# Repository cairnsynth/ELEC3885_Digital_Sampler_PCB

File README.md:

# ELEC3885 Digital Sampler PCB

- Sample-based musical instrument aimed for use in education
- Capable of sequencing and playback of samples on 4 separate channels, and audio effects
- Developed using the Teensy 4.1 development board

## PCB Features

- USB/Li-Po battery power supply
- Audio I/O
	- Line level input/output
	- Headphone output with variable volume
	- Internal MEMS microphone
	- Balanced external microphone input
- User Interface
	- LCD
		- Sample information
		- File browser
		- Parameter values linked to encoders
	- Encoders
		- Control sample specific parameters
	- Potentiometers
		- Control global effects (reverb, filter)
	- RGB LEDs
		- Display sequence playback
	- Button Arrays
		- 8 button array for sample sequencing
		- 4 button array for instant sample playback

---

## Revisions

- Revisions are separated on different branches

### Rev1 (main branch)
- Initial prototype PCB layout containing
	- Teensy 4.1 mounting headers
	- SGTL5000 codec
	- Audio I/O
	- Breakout headers for internal microphone and differential amplifier testing
	- Basic UI

### Rev2
- Layout alterations reducing length of traces for MCU-codec interfaces

### Rev3
- Switch to 4 layer board, 2 sided assembly
	- Analogue circuitry moved to back face
- External microphone differential amplifier added
- Power supply/Li-Po charging circuit added
- Integration of other group members work
	- LCD header and interface routing
	- LED and shift registers
	- Button arrays
	- Encoders/Pots
- Test points added for testing/debugging

### Rev4
- Changes to accommodate JLCPCB stock
	- Codec circuit redesign for QFN32 package of SGTL5000
	- SMD packages
- Trace teardrops added

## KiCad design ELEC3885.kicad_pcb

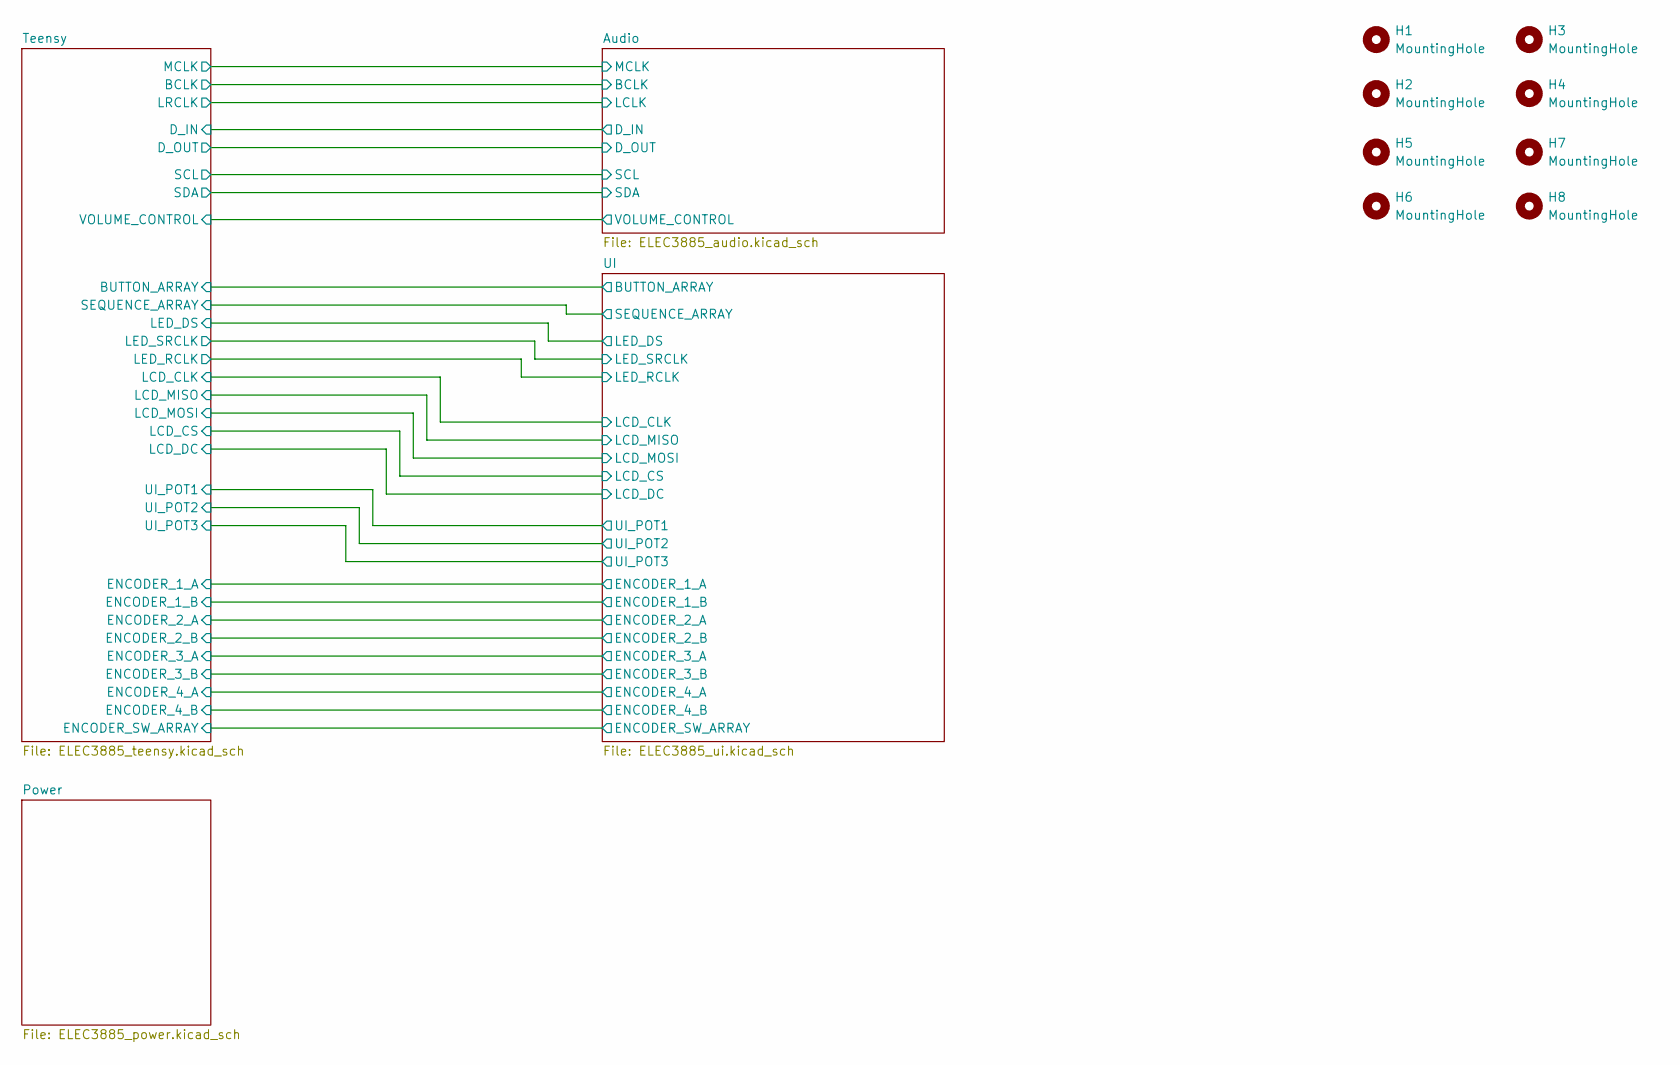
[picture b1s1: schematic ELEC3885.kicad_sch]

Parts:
H1, H2, H3, H4, H5, H6, H7, H8: MountingHole; MountingHole_3.2mm_M3

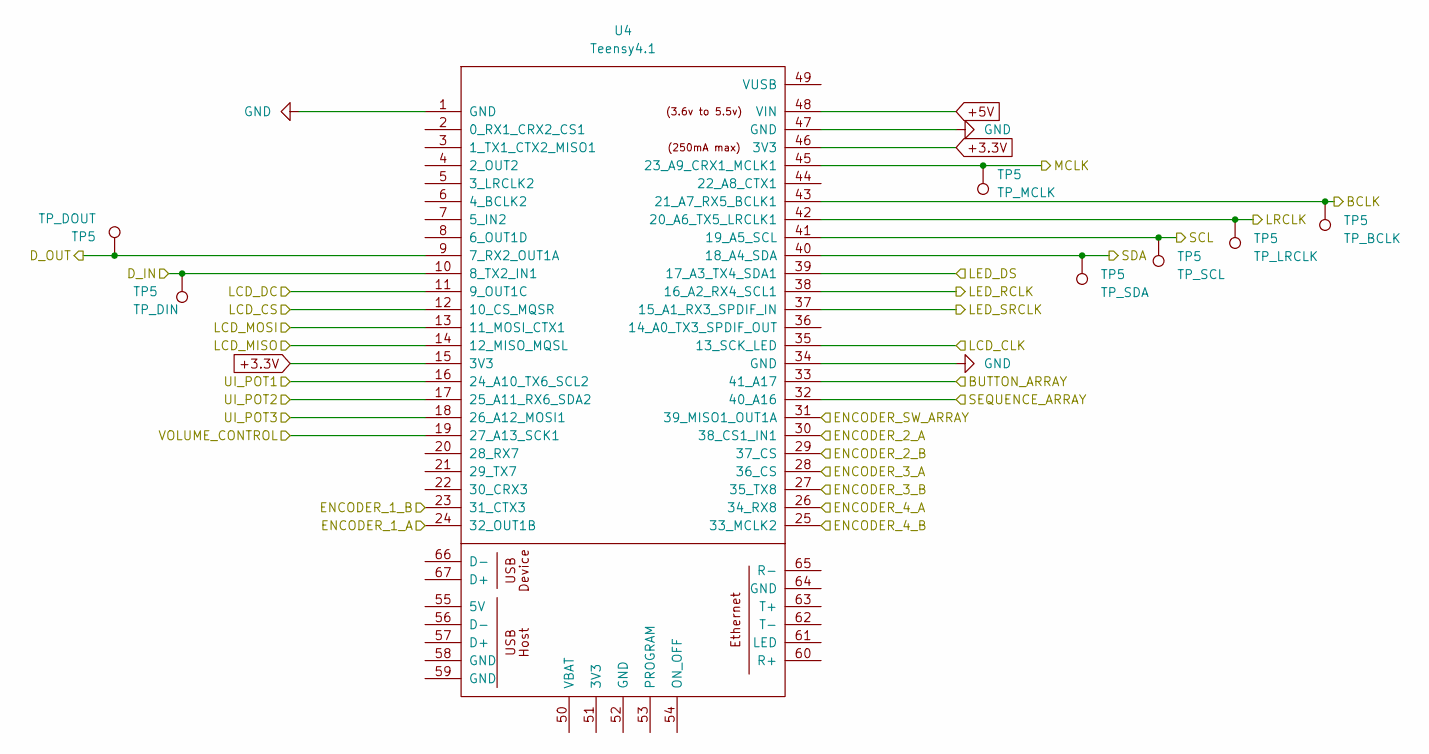
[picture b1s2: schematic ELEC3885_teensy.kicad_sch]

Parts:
TP5: TP_LRCLK; TestPoint_Pad_D1.0mm
U4: Teensy4.1; Teensy41

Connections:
+3.3V: U4.15 (3V3), U4.46 (3V3); also elsewhere on the board
+5V: U4.48 (VIN); also elsewhere on the board
/Audio/VOLUME_CONTROL: U4.19 (27_A13_SCK1); also elsewhere on the board
/Teensy/ENCODER_1_A: U4.24 (32_OUT1B); also elsewhere on the board
/Teensy/ENCODER_1_B: U4.23 (31_CTX3); also elsewhere on the board
/Teensy/ENCODER_2_A: U4.30 (38_CS1_IN1); also elsewhere on the board
/Teensy/ENCODER_2_B: U4.29 (37_CS); also elsewhere on the board
/Teensy/ENCODER_3_A: U4.28 (36_CS); also elsewhere on the board
/Teensy/ENCODER_3_B: U4.27 (35_TX8); also elsewhere on the board
/Teensy/ENCODER_4_A: U4.26 (34_RX8); also elsewhere on the board
/Teensy/ENCODER_4_B: U4.25 (33_MCLK2); also elsewhere on the board
/Teensy/ENCODER_SW_ARRAY: U4.31 (39_MISO1_OUT1A); also elsewhere on the board
/Teensy/LCD_CLK: U4.35 (13_SCK_LED); also elsewhere on the board
/Teensy/LCD_CS: U4.12 (10_CS_MQSR); also elsewhere on the board
/Teensy/LCD_DC: U4.11 (9_OUT1C); also elsewhere on the board
/Teensy/LCD_MISO: U4.14 (12_MISO_MQSL); also elsewhere on the board
/Teensy/LCD_MOSI: U4.13 (11_MOSI_CTX1); also elsewhere on the board
/Teensy/LED_DS: U4.39 (17_A3_TX4_SDA1); also elsewhere on the board
/Teensy/LED_RCLK: U4.38 (16_A2_RX4_SCL1); also elsewhere on the board
/Teensy/LED_SRCLK: U4.37 (15_A1_RX3_SPDIF_IN); also elsewhere on the board
/Teensy/SEQUENCE_ARRAY: U4.32 (40_A16); also elsewhere on the board
/Teensy/UI_POT1: U4.16 (24_A10_TX6_SCL2); also elsewhere on the board
/Teensy/UI_POT2: U4.17 (25_A11_RX6_SDA2); also elsewhere on the board
/Teensy/UI_POT3: U4.18 (26_A12_MOSI1); also elsewhere on the board
GND: U4.1 (GND), U4.34 (GND), U4.47 (GND); also elsewhere on the board

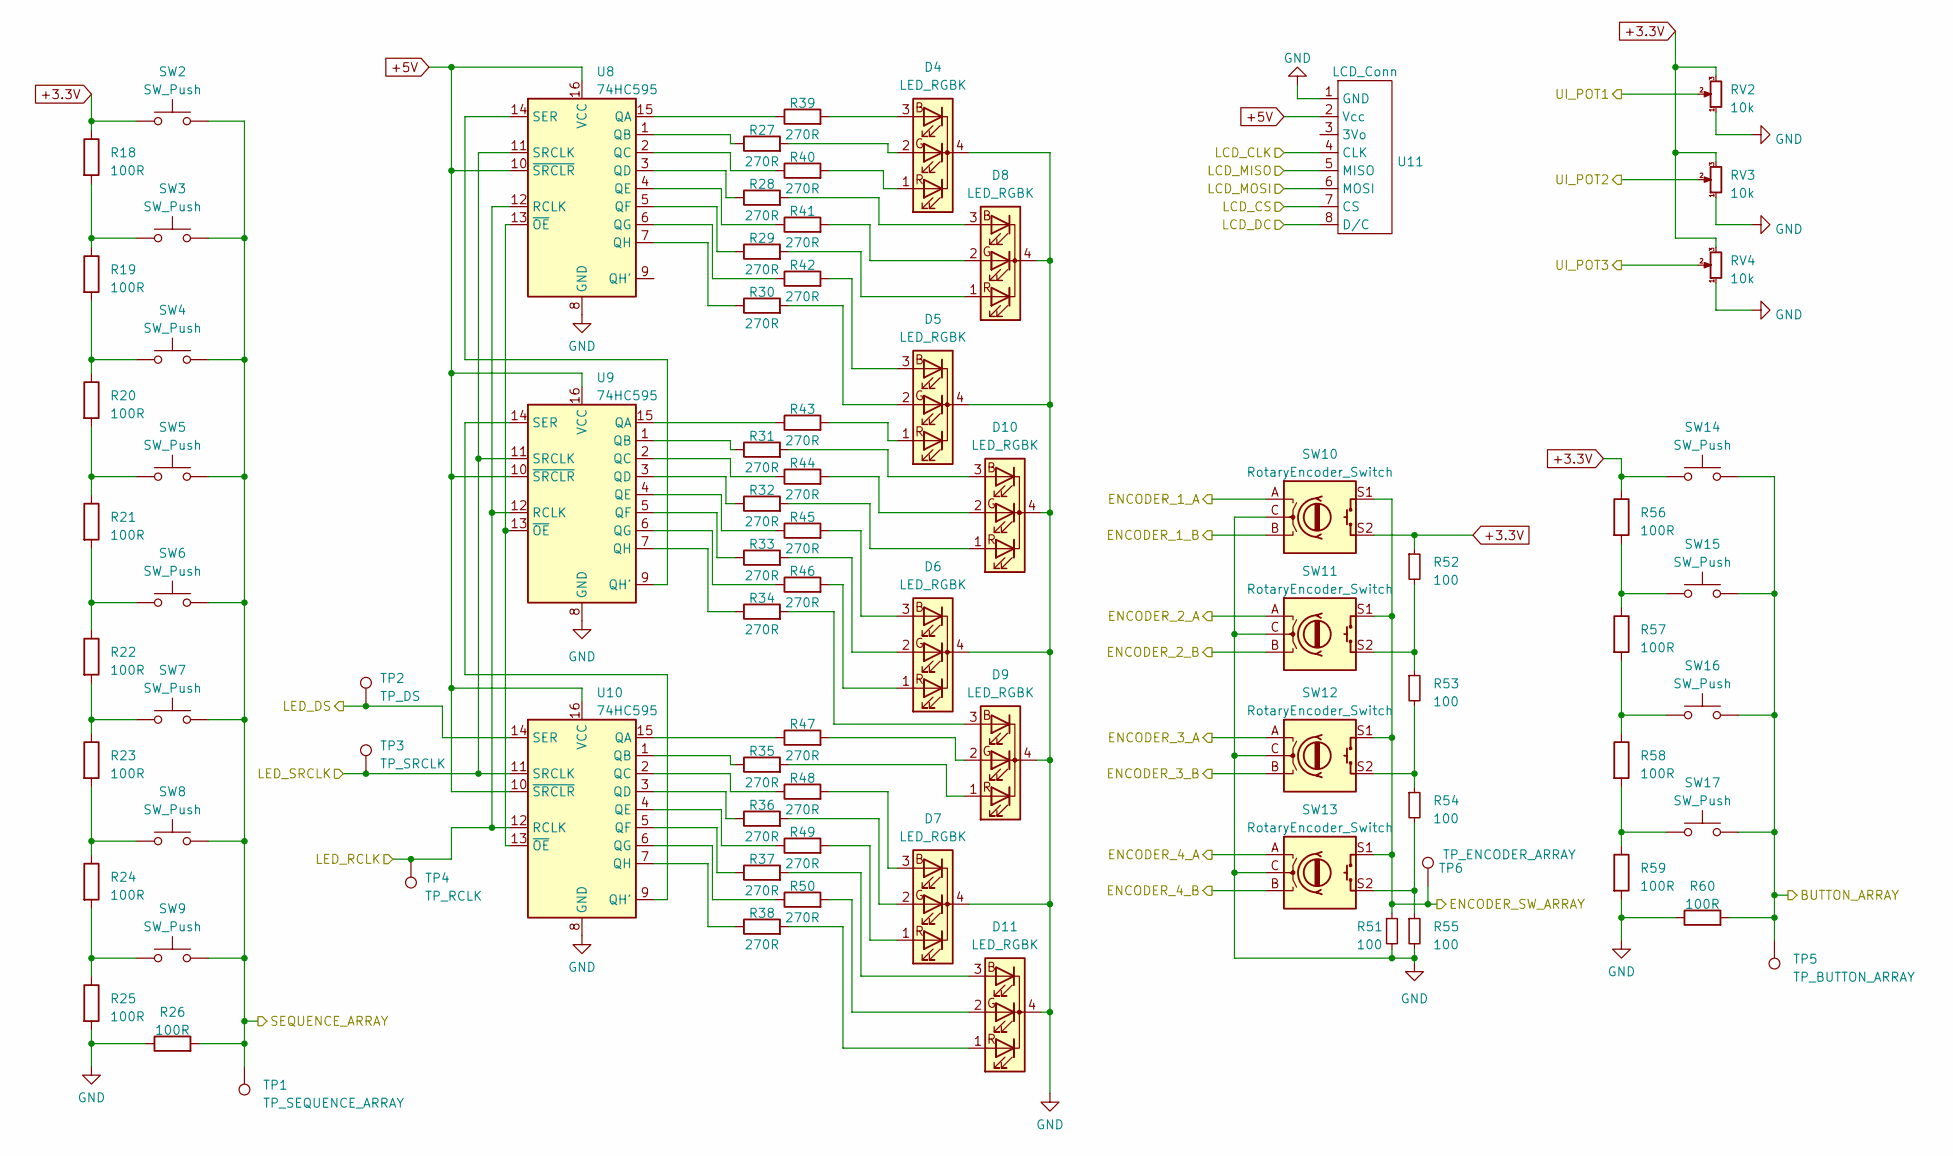
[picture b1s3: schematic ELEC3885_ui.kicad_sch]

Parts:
D4, D5, D6, D7, D8, D9, D10, D11: LED_RGBK; LED_D5.0mm-4_RGB
R18, R19, R20, R21, R22, R23, R24, R25, R26, R56, R57, R58, R59, R60: 100R; R_0402_1005Metric
R27, R28, R29, R30, R31, R32, R33, R34, R35, R36, R37, R38, R39, R40, R41, R42, R43, R44, R45, R46, R47, R48, R49, R50: 270R; R_0402_1005Metric
R51, R52, R53, R54, R55: 100; R_0402_1005Metric
RV2, RV3, RV4: 10k; Potentiometer_Alpha_RD901F-40-00D_Single_Vertical
SW2, SW3, SW4, SW5, SW6, SW7, SW8, SW9, SW14, SW15, SW16, SW17: SW_Push; SW_Cherry_MX_1.00u_PCB
SW10, SW11, SW12, SW13: RotaryEncoder_Switch; RotaryEncoder_Alps_EC11E-Switch_Vertical_H20mm
TP1: TP_SEQUENCE_ARRAY; TestPoint_Pad_D1.0mm
TP2: TP_DS; TestPoint_Pad_D1.0mm
TP3: TP_SRCLK; TestPoint_Pad_D1.0mm
TP4: TP_RCLK; TestPoint_Pad_D1.0mm
TP5: TP_BUTTON_ARRAY; TestPoint_Pad_D1.0mm
TP6: TP_ENCODER_ARRAY; TestPoint_Pad_D1.0mm
U8, U9, U10: 74HC595; SOP-16_3.9x9.9mm_P1.27mm
U11: LCD_Conn; Adafruit_3.5_TFT_SPI

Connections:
+3.3V: R18.1, R52.1, R56.1, RV2.3, RV3.3, RV4.3, SW2.1, SW10.S2, SW14.1; also elsewhere on the board
+5V: U8.10 (~SRCLR), U8.16 (VCC), U9.10 (~SRCLR), U9.16 (VCC), U10.10 (~SRCLR), U10.16 (VCC), U11.2 (Vcc); also elsewhere on the board
/Teensy/ENCODER_1_A: SW10.A; also elsewhere on the board
/Teensy/ENCODER_1_B: SW10.B; also elsewhere on the board
/Teensy/ENCODER_2_A: SW11.A; also elsewhere on the board
/Teensy/ENCODER_2_B: SW11.B; also elsewhere on the board
/Teensy/ENCODER_3_A: SW12.A; also elsewhere on the board
/Teensy/ENCODER_3_B: SW12.B; also elsewhere on the board
/Teensy/ENCODER_4_A: SW13.A; also elsewhere on the board
/Teensy/ENCODER_4_B: SW13.B; also elsewhere on the board
/Teensy/ENCODER_SW_ARRAY: R51.1, SW10.S1, SW11.S1, SW12.S1, SW13.S1, TP6.1; also elsewhere on the board
/Teensy/LCD_CLK: U11.4 (CLK); also elsewhere on the board
/Teensy/LCD_CS: U11.7 (CS); also elsewhere on the board
/Teensy/LCD_DC: U11.8 (D/C); also elsewhere on the board
/Teensy/LCD_MISO: U11.5 (MISO); also elsewhere on the board
/Teensy/LCD_MOSI: U11.6 (MOSI); also elsewhere on the board
/Teensy/LED_DS: TP2.1, U10.14 (SER); also elsewhere on the board
/Teensy/LED_RCLK: TP4.1, U8.12 (RCLK), U9.12 (RCLK), U10.12 (RCLK); also elsewhere on the board
/Teensy/LED_SRCLK: TP3.1, U8.11 (SRCLK), U9.11 (SRCLK), U10.11 (SRCLK); also elsewhere on the board
/Teensy/SEQUENCE_ARRAY: R26.2, SW2.2, SW3.2, SW4.2, SW5.2, SW6.2, SW7.2, SW8.2, SW9.2, TP1.1; also elsewhere on the board
/Teensy/UI_POT1: RV2.2; also elsewhere on the board
/Teensy/UI_POT2: RV3.2; also elsewhere on the board
/Teensy/UI_POT3: RV4.2; also elsewhere on the board
GND: D4.4 (K), D5.4 (K), D6.4 (K), D7.4 (K), D8.4 (K), D9.4 (K), D10.4 (K), D11.4 (K), R25.2, R26.1, R51.2, R55.2, R59.2, R60.1, RV2.1, RV3.1, RV4.1, SW10.C, SW11.C, SW12.C, SW13.C, U8.8 (GND), U9.8 (GND), U10.8 (GND), U11.1 (GND); also elsewhere on the board
unnamed: D4.3 (BA), R39.2
unnamed: D4.2 (GA), R27.2
unnamed: D4.1 (RA), R40.2
unnamed: D5.3 (BA), R42.2
unnamed: D5.2 (GA), R30.2
unnamed: D5.1 (RA), R43.2
unnamed: D6.3 (BA), R45.2
unnamed: D6.2 (GA), R33.2
unnamed: D6.1 (RA), R46.2
unnamed: D7.3 (BA), R48.2
unnamed: D7.2 (GA), R36.2
unnamed: D7.1 (RA), R49.2
unnamed: D8.3 (BA), R28.2
unnamed: D8.2 (GA), R41.2
unnamed: D8.1 (RA), R29.2
unnamed: D9.3 (BA), R34.2
unnamed: D9.2 (GA), R47.2
unnamed: D9.1 (RA), R35.2
unnamed: D10.3 (BA), R31.2
unnamed: D10.2 (GA), R44.2
unnamed: D10.1 (RA), R32.2
unnamed: D11.3 (BA), R37.2
unnamed: D11.2 (GA), R50.2
unnamed: D11.1 (RA), R38.2
unnamed: R18.2, R19.1, SW3.1
unnamed: R19.2, R20.1, SW4.1
unnamed: R20.2, R21.1, SW5.1
unnamed: R21.2, R22.1, SW6.1
unnamed: R22.2, R23.1, SW7.1
unnamed: R23.2, R24.1, SW8.1
unnamed: R24.2, R25.1, SW9.1
unnamed: R52.2, R53.1, SW11.S2
unnamed: R53.2, R54.1, SW12.S2
unnamed: R54.2, R55.1, SW13.S2
unnamed: R56.2, R57.1, SW15.1
unnamed: R57.2, R58.1, SW16.1
unnamed: R58.2, R59.1, SW17.1
unnamed: R39.1, U8.15 (QA)
unnamed: R27.1, U8.1 (QB)
unnamed: R40.1, U8.2 (QC)
unnamed: R28.1, U8.3 (QD)
unnamed: R41.1, U8.4 (QE)
unnamed: R29.1, U8.5 (QF)
unnamed: R42.1, U8.6 (QG)
unnamed: R30.1, U8.7 (QH)
unnamed: U8.14 (SER), U9.9 (QH')
unnamed: R43.1, U9.15 (QA)
unnamed: R31.1, U9.1 (QB)
unnamed: R44.1, U9.2 (QC)
unnamed: R32.1, U9.3 (QD)
unnamed: R45.1, U9.4 (QE)
unnamed: R33.1, U9.5 (QF)
unnamed: R46.1, U9.6 (QG)
unnamed: R34.1, U9.7 (QH)
unnamed: R47.1, U10.15 (QA)
unnamed: R35.1, U10.1 (QB)
unnamed: R48.1, U10.2 (QC)
unnamed: R36.1, U10.3 (QD)
unnamed: R49.1, U10.4 (QE)
unnamed: R37.1, U10.5 (QF)
unnamed: R50.1, U10.6 (QG)
unnamed: U9.14 (SER), U10.9 (QH')
unnamed: R38.1, U10.7 (QH)
unnamed: U8.13 (~OE), U9.13 (~OE), U10.13 (~OE)

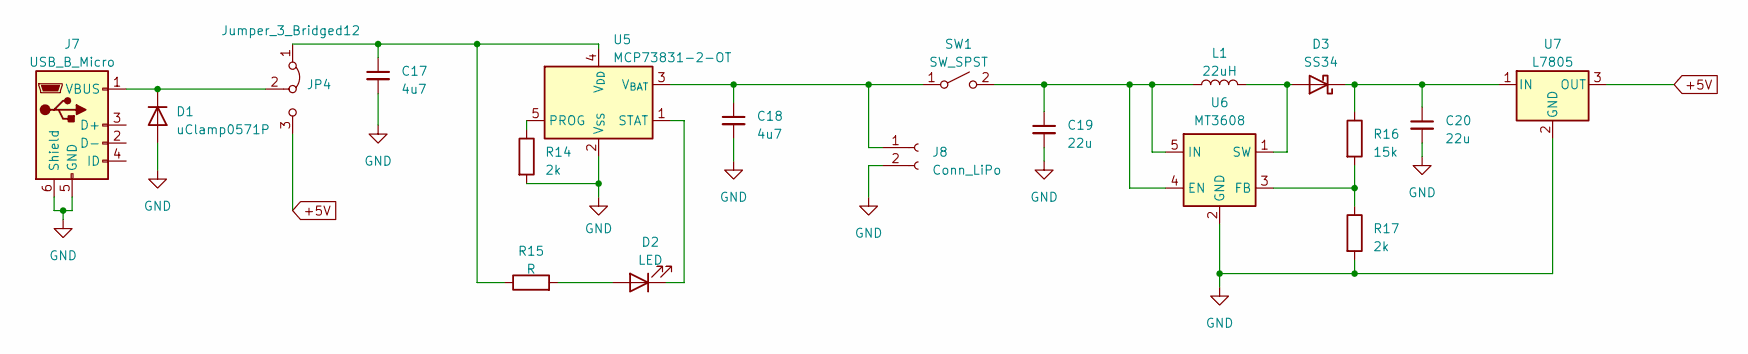
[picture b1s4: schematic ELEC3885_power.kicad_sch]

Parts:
C17, C18: 4u7; C_0603_1608Metric
C19, C20: 22u; C_0603_1608Metric
D1: uClamp0571P; DFN1610-2
D2: LED; LED_0603_1608Metric
D3: SS34; D_SMC
J7: USB_B_Micro; USB_Micro-B_MicroXNJ_Horizontal
J8: Conn_LiPo; JST_EH_S2B-EH_1x02_P2.50mm_Horizontal
JP4: Jumper_3_Bridged12; SolderJumper-3_P1.3mm_Bridged2Bar12_RoundedPad1.0x1.5mm_Num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
L1: 22uH; L_10.4x10.4_H4.8
R14, R17: 2k; R_0402_1005Metric
R15: R; R_0402_1005Metric
R16: 15k; R_0603_1608Metric
SW1: SW_SPST; SW_CuK_OS102011MA1QN1_SPDT_Angled
U5: MCP73831-2-OT; SOT-23-5
U6: MT3608; SOT-23-6
U7: L7805; TO-252-2

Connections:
+5V: JP4.3 (B), U7.3 (OUT); also elsewhere on the board
GND: C17.2, C18.2, C19.2, C20.2, D1.2 (A), J7.5 (GND), J7.6 (Shield), J8.2, R14.2, R17.2, U5.2 (V_{SS}), U6.2 (GND), U7.2 (GND); also elsewhere on the board
unnamed: D1.1 (K), J7.1 (VBUS), JP4.2 (C)
unnamed: D2.2 (A), R15.2
unnamed: D2.1 (K), U5.1 (STAT)
unnamed: D3.2 (A), L1.2, U6.1 (SW)
unnamed: C20.1, D3.1 (K), R16.1, U7.1 (IN)
unnamed: C18.1, J8.1, SW1.1 (A), U5.3 (V_{BAT})
unnamed: C17.1, JP4.1 (A), R15.1, U5.4 (V_{DD})
unnamed: C19.1, L1.1, SW1.2 (B), U6.4 (EN), U6.5 (IN)
unnamed: R14.1, U5.5 (PROG)
unnamed: R16.2, R17.1, U6.3 (FB)

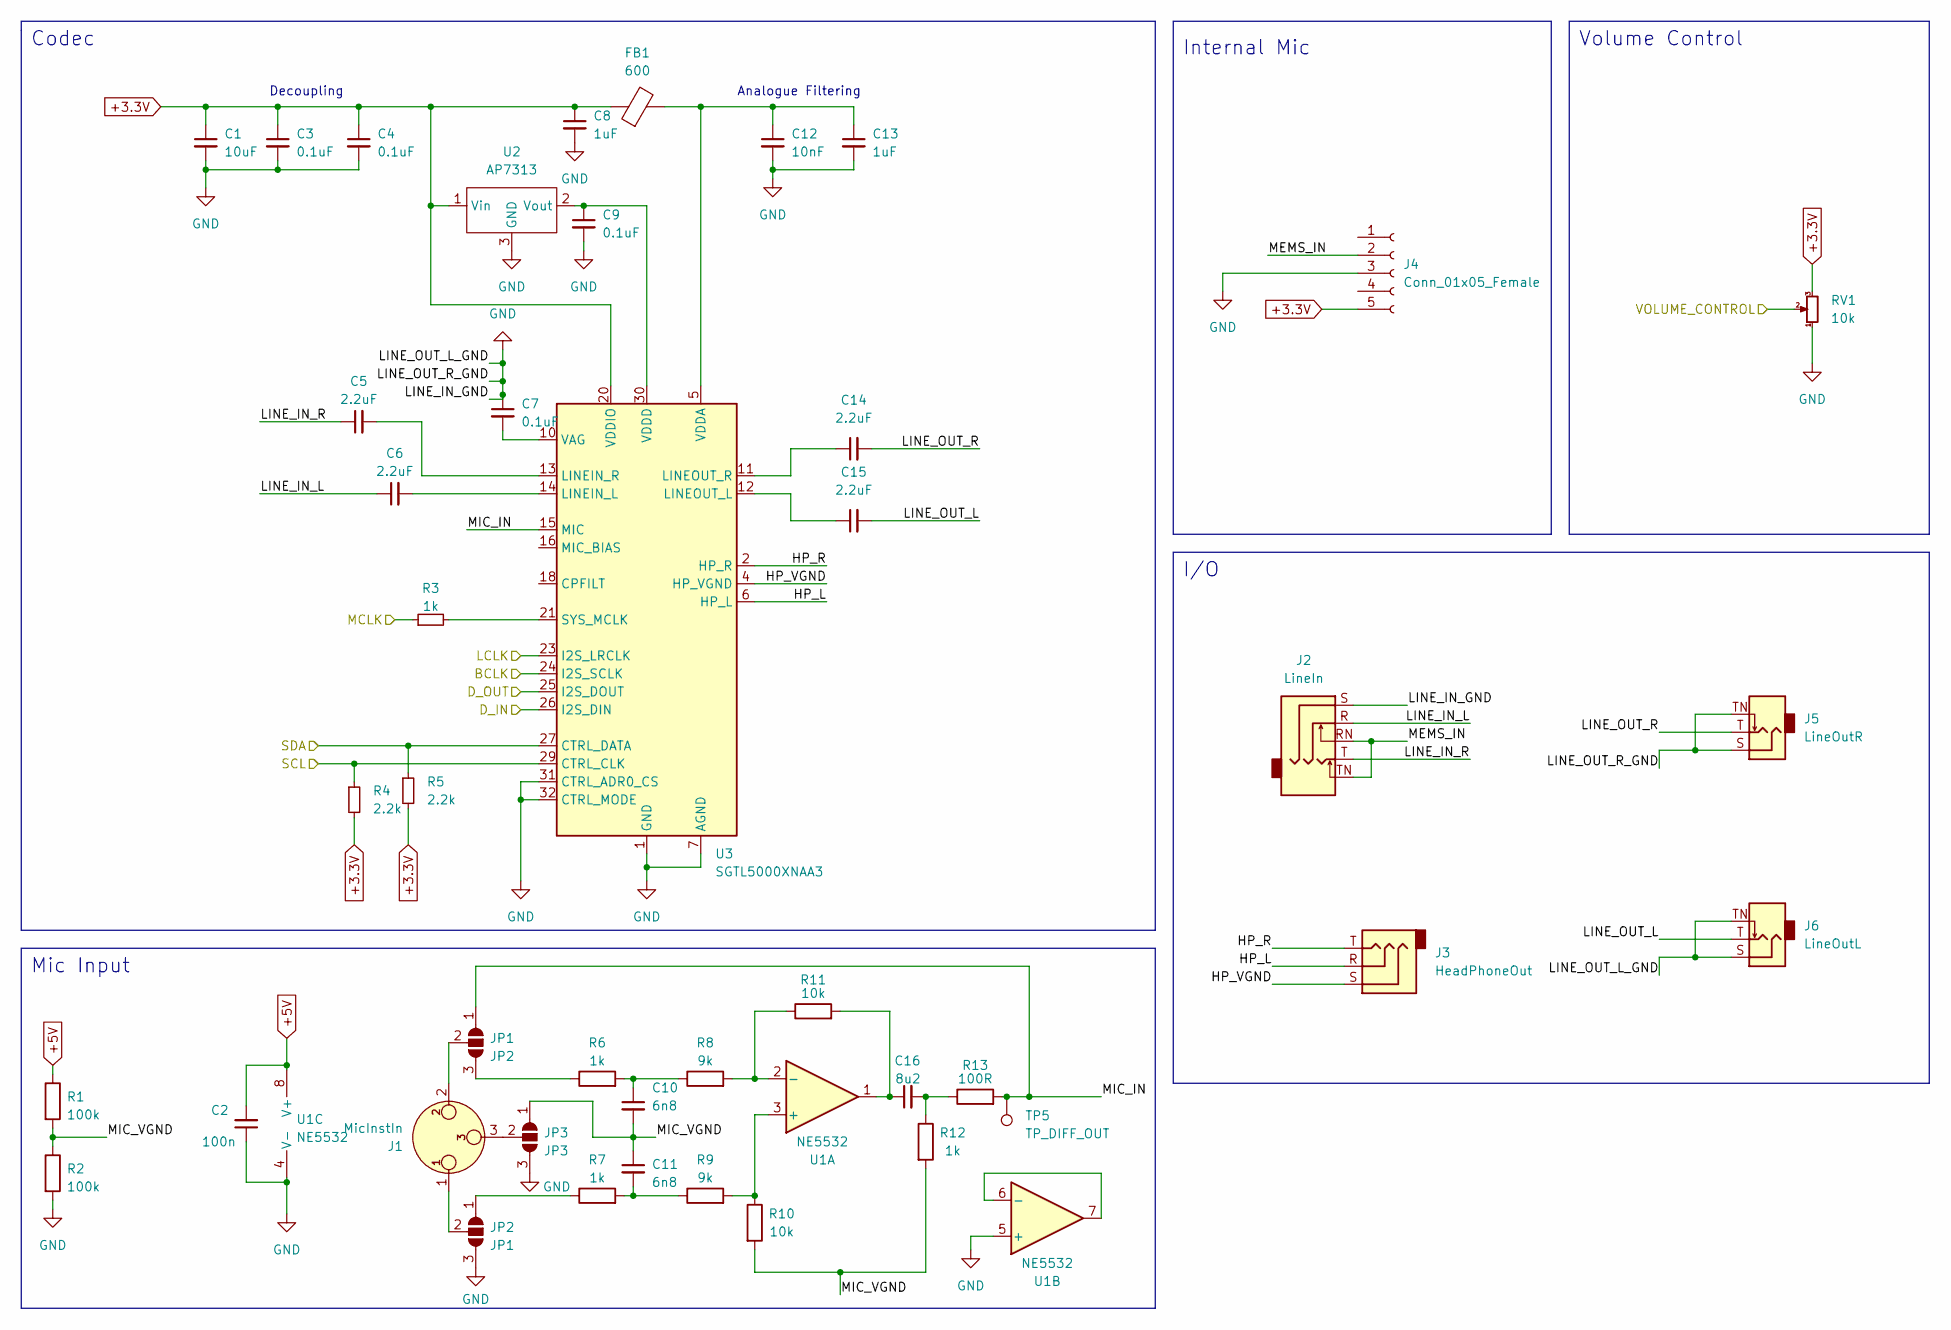
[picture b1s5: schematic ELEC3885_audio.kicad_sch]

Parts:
C1: 10uF; C_0603_1608Metric
C2: 100n; C_0402_1005Metric
C3, C4, C7, C9: 0.1uF; C_0402_1005Metric
C5, C6, C14, C15: 2.2uF; C_0603_1608Metric
C8, C13: 1uF; C_0402_1005Metric
C10, C11: 6n8; C_0402_1005Metric
C12: 10nF; C_0402_1005Metric
C16: 8u2; C_0603_1608Metric
FB1: 600; L_0603_1608Metric
J1: MicInstIn; Jack_XLR_Neutrik_NC3FAAH-0_Horizontal
J2: LineIn; Jack_3.5mm_CUI_SJ1-3535NG_Horizontal
J3: HeadPhoneOut; Jack_3.5mm_CUI_SJ1-3533NG_Horizontal
J4: Conn_01x05_Female; PinSocket_1x05_P2.54mm_Vertical
J5: LineOutR; Jack_6.35mm_Neutrik_NMJ4HCD2_Horizontal
J6: LineOutL; Jack_6.35mm_Neutrik_NMJ4HCD2_Horizontal
JP1: JP2; SolderJumper-3_P1.3mm_Open_RoundedPad1.0x1.5mm
JP2: JP1; SolderJumper-3_P1.3mm_Open_RoundedPad1.0x1.5mm
JP3: JP3; SolderJumper-3_P1.3mm_Open_RoundedPad1.0x1.5mm
R1, R2: 100k; R_0603_1608Metric
R3, R6, R7, R12: 1k; R_0402_1005Metric
R4, R5: 2.2k; R_0402_1005Metric
R8, R9: 9k; R_0805_2012Metric
R10, R11: 10k; R_0603_1608Metric
R13: 100R; R_0402_1005Metric
RV1: 10k; Potentiometer_Alpha_RD901F-40-00D_Single_Vertical
TP5: TP_DIFF_OUT; TestPoint_Pad_D1.0mm
U1: NE5532; SOIC-8-1EP_3.9x4.9mm_P1.27mm_EP2.29x3mm
U2: AP7313; SOT23
U3: SGTL5000XNAA3; QFN-32-1EP_5x5mm_P0.5mm_EP3.6x3.6mm

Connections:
+3.3V: C1.1, C3.1, C4.1, C8.1, FB1.1, J4.5, R4.2, R5.2, RV1.3, U2.1 (Vin), U3.20 (VDDIO); also elsewhere on the board
+5V: C2.2, R1.1, U1.8 (V+); also elsewhere on the board
/Audio/HP_L: J3.R, U3.6 (HP_L)
/Audio/HP_R: J3.T, U3.2 (HP_R)
/Audio/HP_VGND: J3.S, U3.4 (HP_VGND)
/Audio/LINE_IN_L: C6.1, J2.R
/Audio/LINE_IN_R: C5.1, J2.T
/Audio/LINE_OUT_L: C15.2, J6.T
/Audio/LINE_OUT_R: C14.2, J5.T
/Audio/MEMS_IN: J2.RN, J2.TN, J4.2
/Audio/MIC_VGND: C10.2, C11.1, JP3.1 (A), R1.2, R2.1, R10.2, R12.2
/Audio/VOLUME_CONTROL: RV1.2; also elsewhere on the board
GND: C1.2, C2.1, C3.2, C4.2, C7.1, C8.2, C9.2, C12.2, C13.2, J2.S, J4.3, J5.S, J5.TN, J6.S, J6.TN, JP2.3 (B), JP3.3 (B), R2.2, RV1.1, U1.4 (V-), U1.5 (+), U2.3 (GND), U3.1 (GND), U3.3 (GND), U3.7 (AGND), U3.31 (CTRL_ADR0_CS), U3.32 (CTRL_MODE), U3.33 (GND); also elsewhere on the board
unnamed: C10.1, R6.2, R8.1
unnamed: C11.2, R7.2, R9.1
unnamed: C16.1, R11.2, U1.1
unnamed: C16.2, R12.1, R13.1
unnamed: JP1.3 (B), R6.1
unnamed: J1.2, JP1.2 (C)
unnamed: JP2.1 (A), R7.1
unnamed: J1.1, JP2.2 (C)
unnamed: J1.3, JP3.2 (C)
unnamed: R9.2, R10.1, U1.3 (+)
unnamed: R8.2, R11.1, U1.2 (-)
unnamed: U1.6 (-), U1.7
unnamed: C9.1, U2.2 (Vout), U3.30 (VDDD)
unnamed: C6.2, U3.14 (LINEIN_L)
unnamed: C5.2, U3.13 (LINEIN_R)
unnamed: C15.1, U3.12 (LINEOUT_L)
unnamed: C14.1, U3.11 (LINEOUT_R)
unnamed: R3.2, U3.21 (SYS_MCLK)
unnamed: C7.2, U3.10 (VAG)
unnamed: C12.1, C13.1, FB1.2, U3.5 (VDDA)

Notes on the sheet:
Decoupling
Internal Mic
I/O
Volume Control
Codec
Mic Input
Analogue Filtering

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
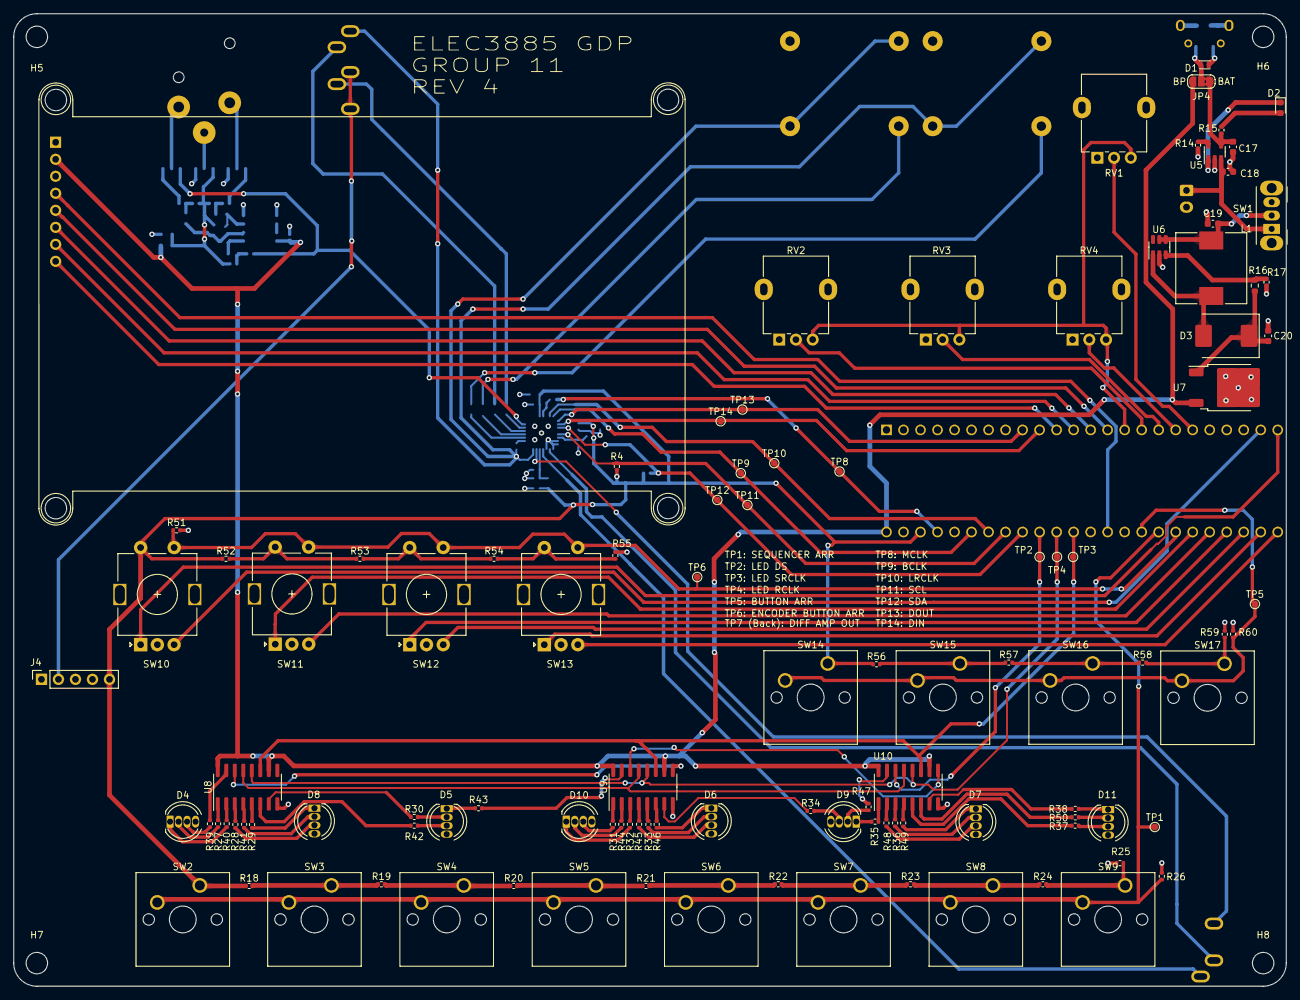
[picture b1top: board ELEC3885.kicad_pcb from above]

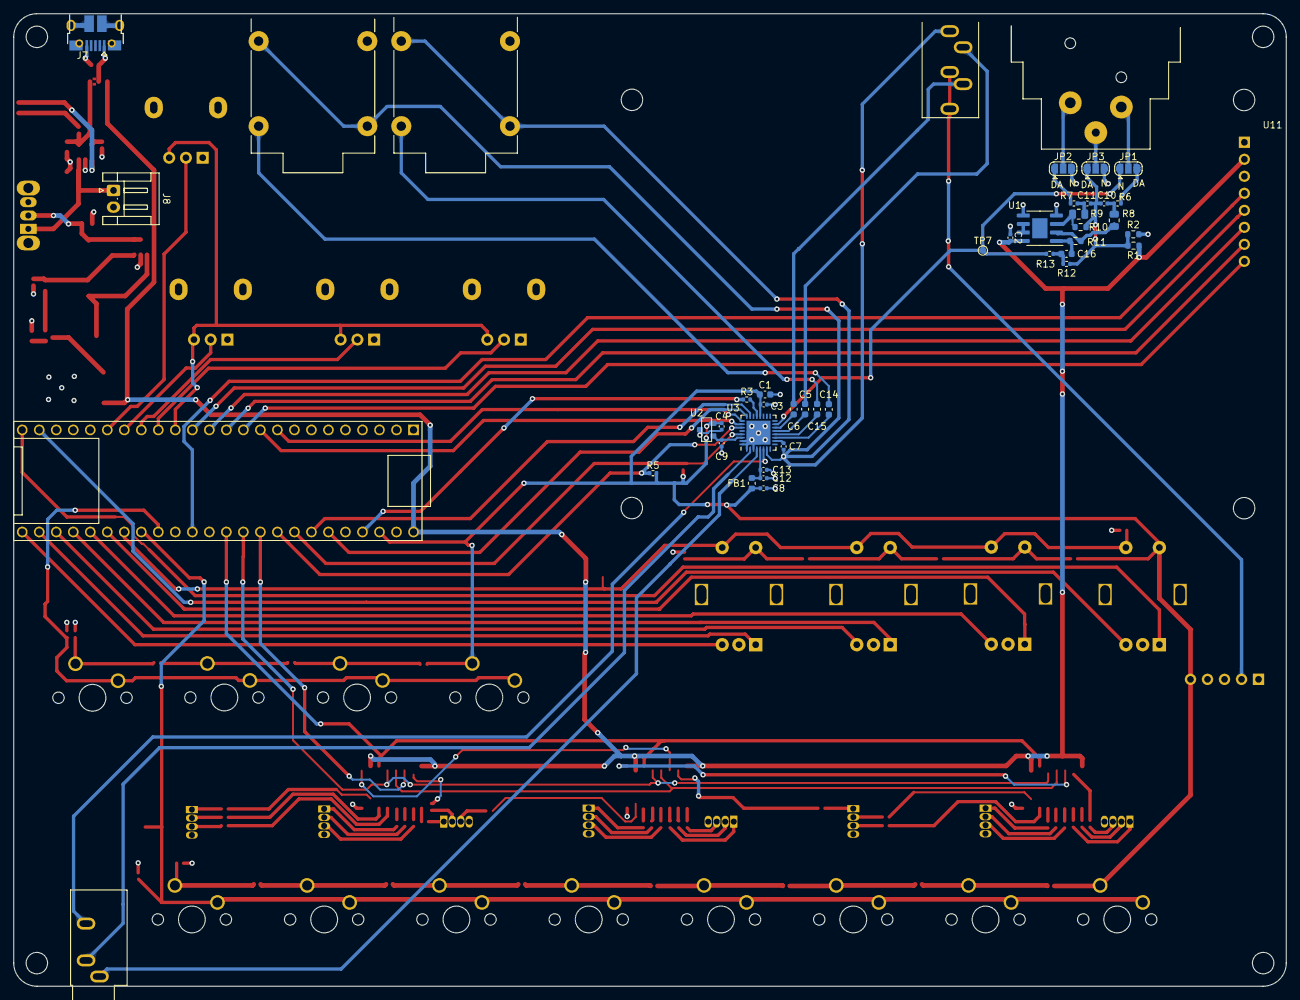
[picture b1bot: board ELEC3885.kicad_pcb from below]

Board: 4 copper layers, 190.0 x 145.2 mm, 159 parts (44 on the bottom side), 137 nets.

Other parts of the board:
TP7: TP_DIFF_OUT; TestPoint_Pad_D1.0mm
TP8: TP_MCLK; TestPoint_Pad_D1.0mm
TP9: TP_BCLK; TestPoint_Pad_D1.0mm
TP10: TP_LRCLK; TestPoint_Pad_D1.0mm
TP11: TP_SCL; TestPoint_Pad_D1.0mm
TP12: TP_SDA; TestPoint_Pad_D1.0mm
TP13: TP_DOUT; TestPoint_Pad_D1.0mm
TP14: TP_DIN; TestPoint_Pad_D1.0mm

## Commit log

2023-01-16 rearrange
2023-01-16 PCB/ rm
2023-01-16 Audio board schematic added
2023-01-16 Audio connections and internal mic added
2023-01-16 Hierarchical sheets setup
2023-01-19 Schematic work
2023-01-20 Initial schematic complete
2023-01-31 New Revision
2023-01-31 Increase track widths
2023-02-02 Fab cleanup, trace tapers added
2023-02-03 AP7313 Fix
2023-02-07 Track Cleanup
2023-03-26 Moved to Rev 3, button + LED ui added
2023-03-26 UI testpoints added
2023-03-28 Rev3 PCB layout started
2023-04-03 Rev3 rework, diff amp jumpers added
2023-04-03 LCD footprint fix
2023-04-17 Encoders, RGB LED added, PCB cleanup
2023-04-18 Rev3 layout work
2023-04-18 Testpoints added, silkscreen cleaned
2023-04-19 LED foorprint fix, ground planes fix
2023-04-19 Rev4 started, changing packages
2023-04-19 Footprints updated except codec
2023-04-19 SGTL5000 package switched to QFN32
2023-04-19 Fix unconnected tracks, add teardrops
2023-04-20 Rev4 ordered
